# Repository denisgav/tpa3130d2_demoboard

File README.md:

The link to the amplifier: https://www.youtube.com/watch?v=wCYNTt5krDM&ab_channel=Phil%E2%80%99sLab
Trying to do it in KiCad...

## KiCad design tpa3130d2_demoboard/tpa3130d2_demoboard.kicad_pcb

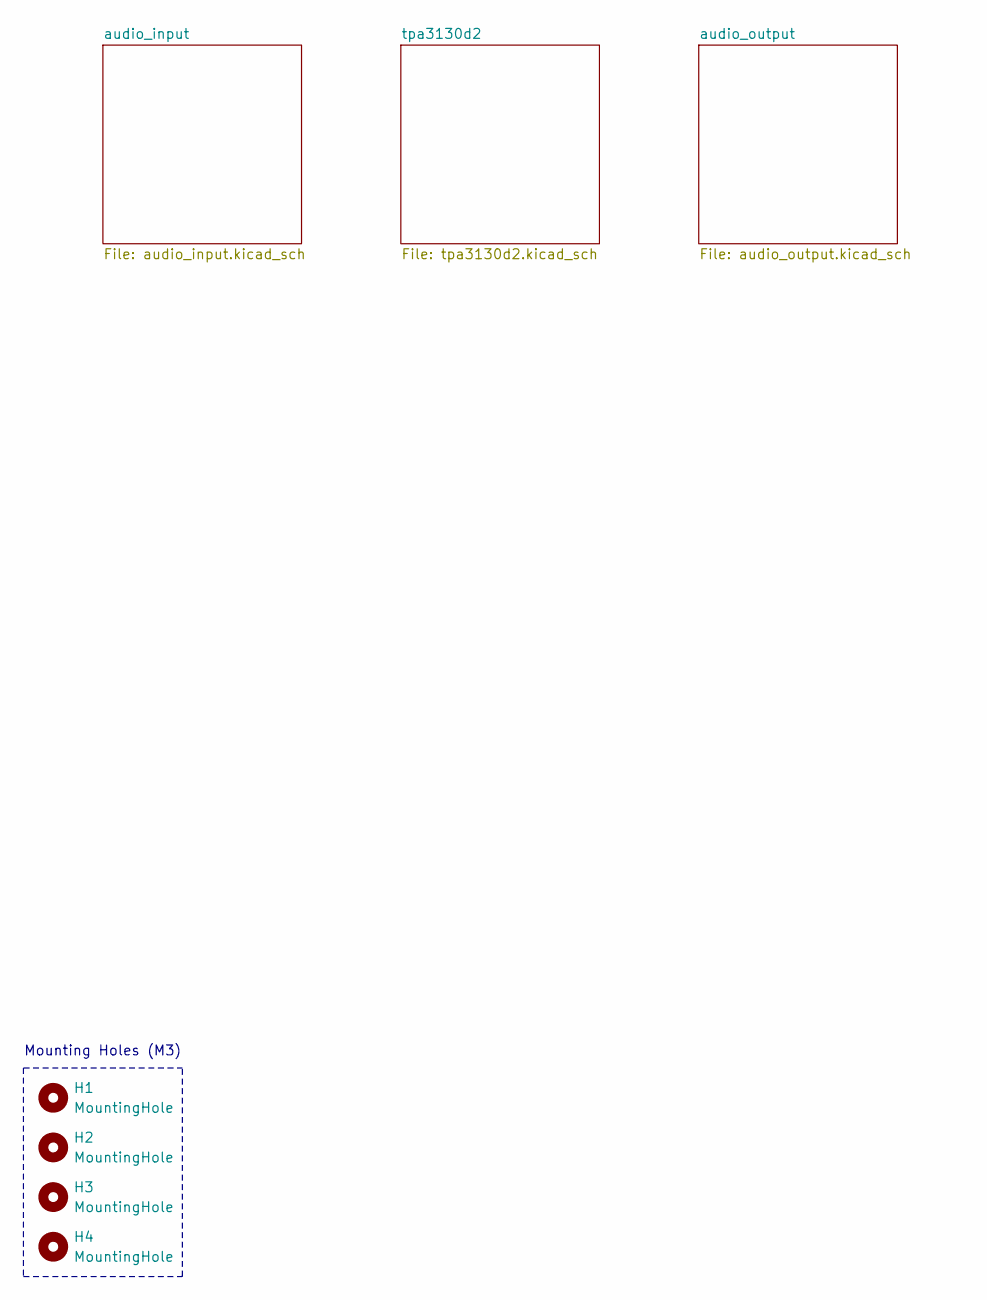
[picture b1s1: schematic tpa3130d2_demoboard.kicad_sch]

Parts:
H1, H2, H3, H4: MountingHole; MountingHole_3.2mm_M3

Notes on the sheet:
Mounting Holes (M3)

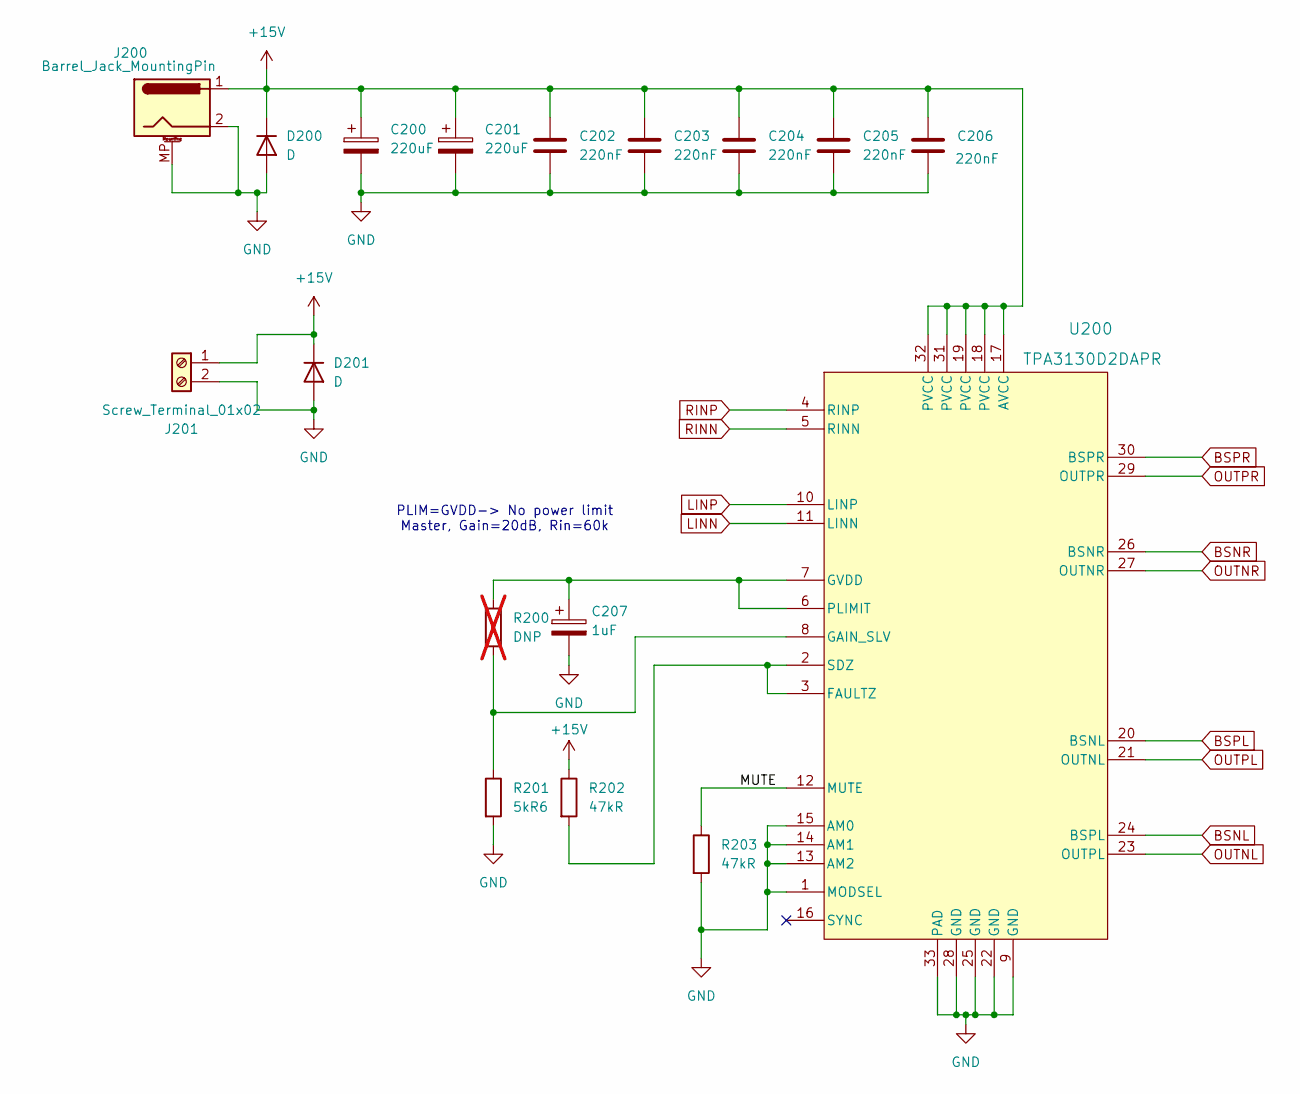
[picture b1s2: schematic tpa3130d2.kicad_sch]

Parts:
C200, C201: 220uF; CP_Radial_D6.3mm_P2.50mm; Part Number 25YXJ220M6.3X11
C202, C203, C204, C205, C206: 220nF; C_0603_1608Metric; Part Number CL10B224KA8NNNC
C207: 1uF; CP_EIA-3216-18_Kemet-A; Part Number TAJA105K035RNJ
D200, D201: D; D_PowerDI-123; Part Number SBR3M30P1-7
J200: Barrel_Jack_MountingPin; BarrelJack_GCT_DCJ200-10-A_Horizontal; Part Number DC-005-A200
J201: Screw_Terminal_01x02; terminal_block; Part Number WJ500V-5.08-2P
R200: DNP; R_0603_1608Metric; not fitted
R201: 5kR6; R_0603_1608Metric; Part Number 0603WAF5601T5E
R202, R203: 47kR; R_0603_1608Metric; Part Number 0603WAJ0473T5E
U200: TPA3130D2DAPR; TPA3130D2DAPR_M; Part Number TPA3130D2DAPR

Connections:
+15V: C200.1, C201.1, C202.1, C203.1, C204.1, C205.1, C206.1, D200.1 (K), D201.1 (K), J200.1, J201.1, R202.1, U200.17 (AVCC), U200.18 (PVCC), U200.19 (PVCC), U200.31 (PVCC), U200.32 (PVCC)
/tpa3130d2/MUTE: R203.1, U200.12 (MUTE)
BSNL: U200.24 (BSPL); also elsewhere on the board
BSNR: U200.26 (BSNR); also elsewhere on the board
BSPL: U200.20 (BSNL); also elsewhere on the board
BSPR: U200.30 (BSPR); also elsewhere on the board
GND: C200.2, C201.2, C202.2, C203.2, C204.2, C205.2, C206.2, C207.2, D200.2 (A), D201.2 (A), J200.2, J200.MP (MountPin), J201.2, R201.2, R203.2, U200.1 (MODSEL), U200.9 (GND), U200.13 (AM2), U200.14 (AM1), U200.15 (AM0), U200.22 (GND), U200.25 (GND), U200.28 (GND), U200.33 (PAD); also elsewhere on the board
LINN: U200.11 (LINN); also elsewhere on the board
LINP: U200.10 (LINP); also elsewhere on the board
unnamed: R202.2, U200.2 (SDZ), U200.3 (FAULTZ)
unnamed: R200.2, R201.1, U200.8 (GAIN_SLV)
unnamed: C207.1, R200.1, U200.6 (PLIMIT), U200.7 (GVDD)
OUTNL: U200.23 (OUTPL); also elsewhere on the board
OUTNR: U200.27 (OUTNR); also elsewhere on the board
OUTPL: U200.21 (OUTNL); also elsewhere on the board
OUTPR: U200.29 (OUTPR); also elsewhere on the board
RINN: U200.5 (RINN); also elsewhere on the board
RINP: U200.4 (RINP); also elsewhere on the board

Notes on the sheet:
PLIM=GVDD-> No power limit Master, Gain=20dB, Rin=60k

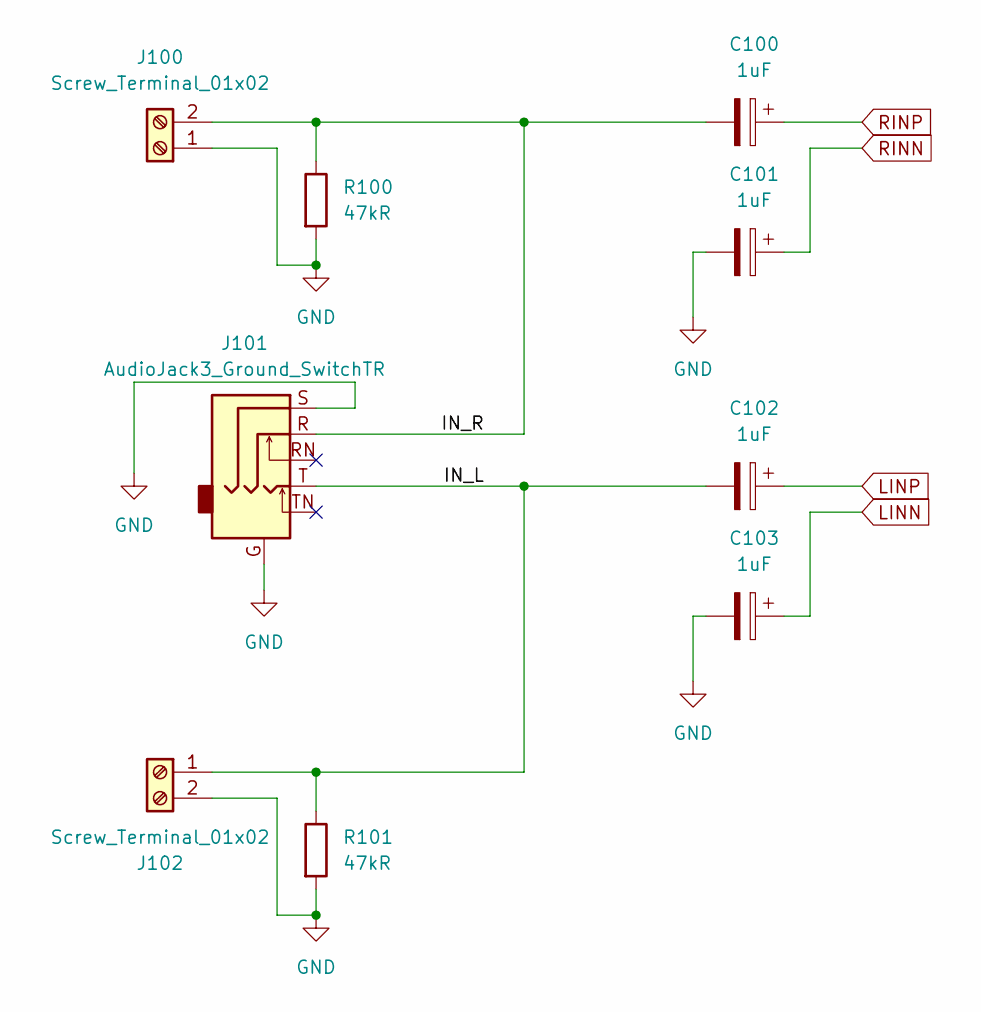
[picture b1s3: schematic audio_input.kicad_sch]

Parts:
C100, C101, C102, C103: 1uF; CP_EIA-3216-18_Kemet-A; Part Number TAJA105K035RNJ
J100, J102: Screw_Terminal_01x02; terminal_block; Part Number WJ500V-5.08-2P
J101: AudioJack3_Ground_SwitchTR; AudioJack_3.5mm_PJ311
R100, R101: 47kR; R_0603_1608Metric; Part Number 0603WAJ0473T5E

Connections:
/audio_input/IN_L: C102.2, J101.T, J102.1, R101.1
/audio_input/IN_R: C100.2, J100.2, J101.R, R100.1
GND: C101.2, C103.2, J100.1, J101.G, J101.S, J102.2, R100.2, R101.2; also elsewhere on the board
LINN: C103.1; also elsewhere on the board
LINP: C102.1; also elsewhere on the board
RINN: C101.1; also elsewhere on the board
RINP: C100.1; also elsewhere on the board

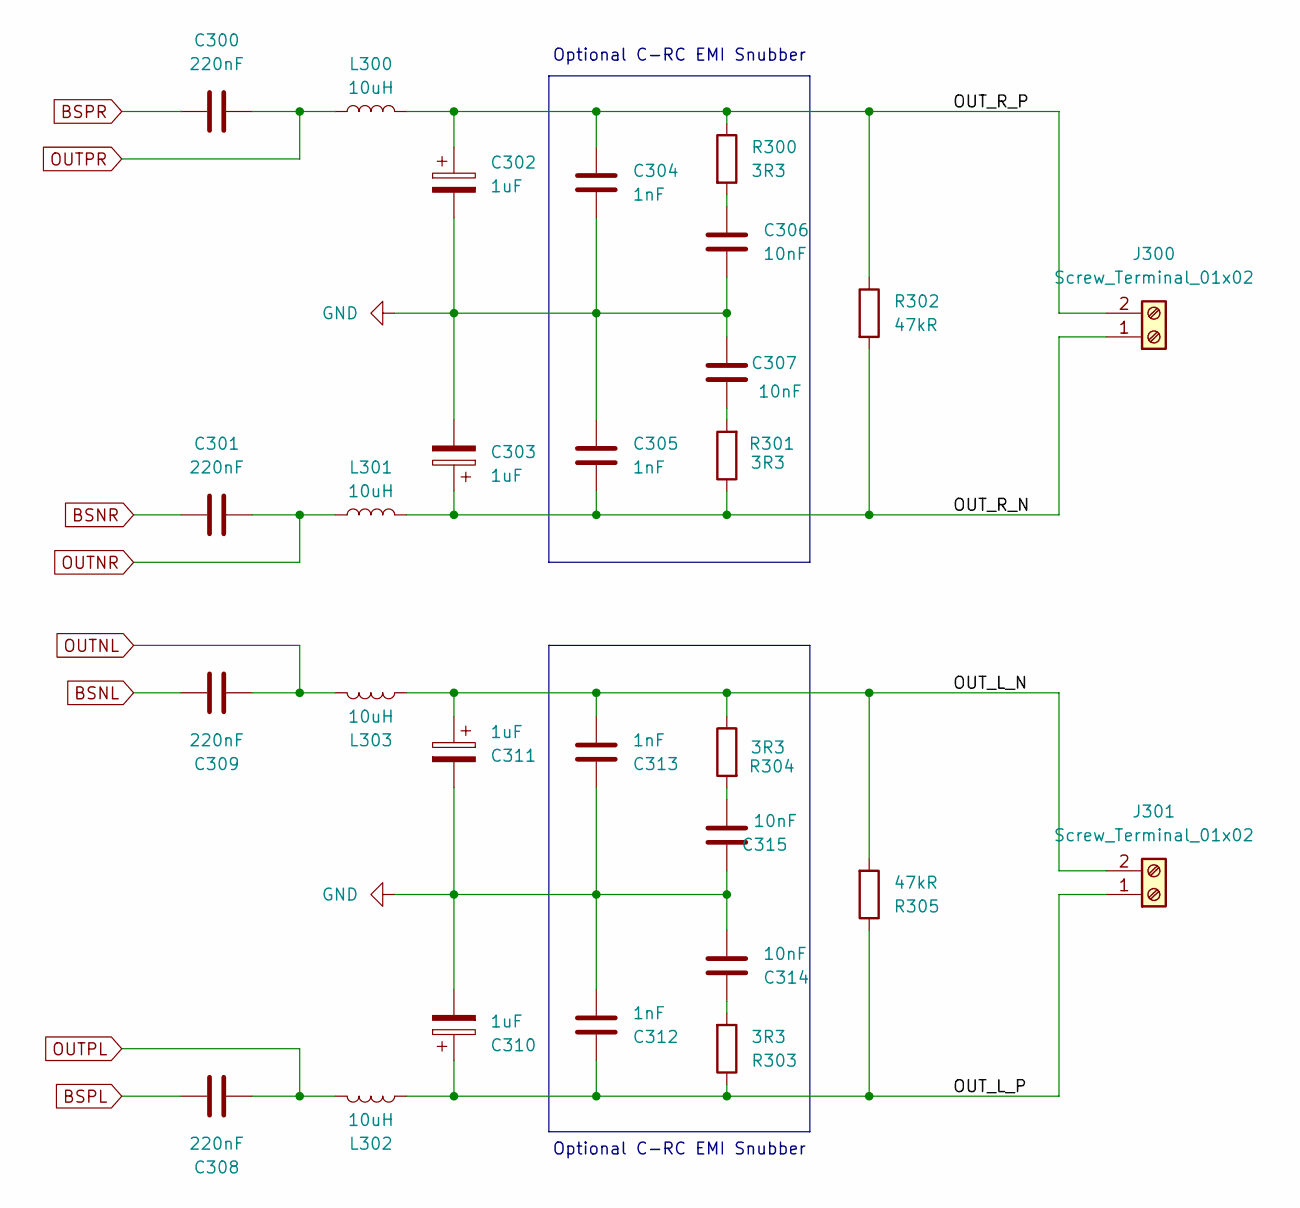
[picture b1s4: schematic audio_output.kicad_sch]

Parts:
C300, C301, C308, C309: 220nF; C_0603_1608Metric; Part Number CL10B224KA8NNNC
C302, C303, C310, C311: 1uF; CP_EIA-3216-18_Kemet-A; Part Number TAJA105K035RNJ
C304, C305, C312, C313: 1nF; C_0603_1608Metric; Part Number CL10B102KB8NNNC
C306, C307, C314, C315: 10nF; C_0603_1608Metric; Part Number CL10B104KB8NNNC
J300, J301: Screw_Terminal_01x02; terminal_block; Part Number WJ500V-5.08-2P
L300, L301, L302, L303: 10uH; Inductor_CYA0630-10UH; Part Number CYA0630-10UH
R300, R301, R303, R304: 3R3; R_0603_1608Metric; Part Number 0603WAF300KT5E
R302, R305: 47kR; R_0603_1608Metric; Part Number 0603WAJ0473T5E

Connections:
/audio_output/OUT_L_N: C311.1, C313.2, J301.2, L303.2, R304.1, R305.2
/audio_output/OUT_L_P: C310.1, C312.1, J301.1, L302.2, R303.1, R305.1
/audio_output/OUT_R_N: C303.1, C305.2, J300.1, L301.2, R301.1, R302.2
/audio_output/OUT_R_P: C302.1, C304.1, J300.2, L300.2, R300.1, R302.1
BSNL: C309.1; also elsewhere on the board
BSNR: C301.1; also elsewhere on the board
BSPL: C308.1; also elsewhere on the board
BSPR: C300.1; also elsewhere on the board
GND: C302.2, C303.2, C304.2, C305.1, C306.2, C307.2, C310.2, C311.2, C312.2, C313.1, C314.2, C315.2; also elsewhere on the board
unnamed: C306.1, R300.2
unnamed: C307.1, R301.2
unnamed: C314.1, R303.2
unnamed: C315.1, R304.2
OUTNL: C309.2, L303.1; also elsewhere on the board
OUTNR: C301.2, L301.1; also elsewhere on the board
OUTPL: C308.2, L302.1; also elsewhere on the board
OUTPR: C300.2, L300.1; also elsewhere on the board

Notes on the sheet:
Optional C-RC EMI Snubber

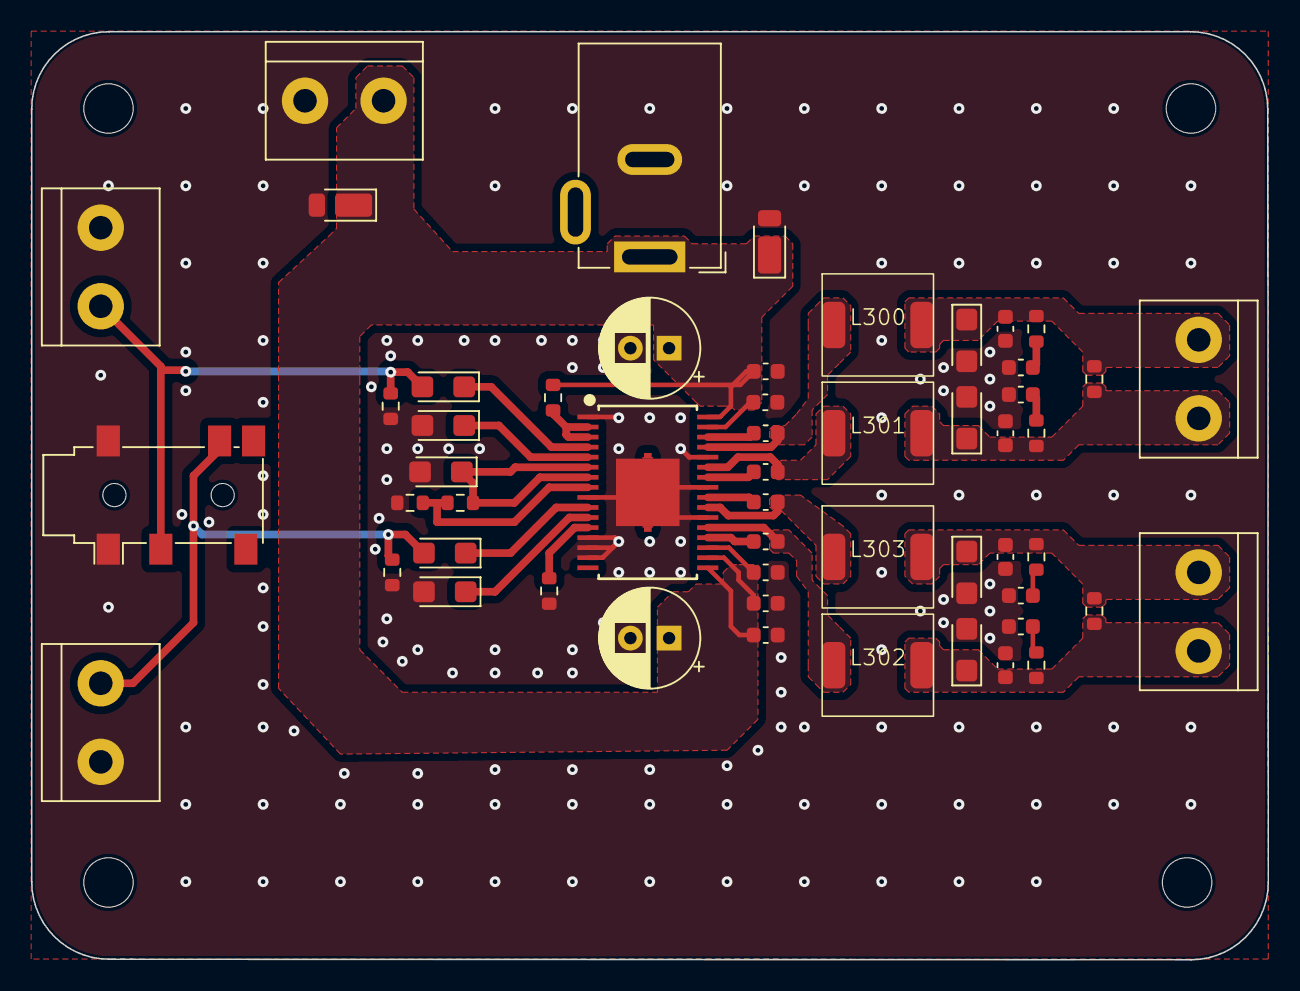
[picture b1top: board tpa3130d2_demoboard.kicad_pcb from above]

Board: 2 copper layers, 80.0 x 60.0 mm, 58 parts (0 on the bottom side), 28 nets.

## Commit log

2025-01-31 Split scheme
2025-01-31 Scheme complete
2025-01-31 Fill BOM
2025-01-31 Footprint updates
2025-02-01 Initial PCB layout
2025-02-01 Minor changes in terminal block footprint
2025-02-04 Initial PCB routing
2025-02-05 Copper fill updates
2025-02-05 DRC fixes
